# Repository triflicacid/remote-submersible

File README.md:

# Remote Control Submersible

This repository holds the custom-written software for a remote control submersible.
There is software for both the on- and off-board controllers.
Hardware overview:

- STM32 L476R chip.
- RFM98W radio module.

Both chips are configured using the STM32CubeMX IDE.

## Folder Layout

- `code` - contains various source code files.
  - `libs` contains common library files.
  - `tests` contains test projects for various components.
  - `unused` contains old unused library or miscellaneous files.
- `schematics` - contains schematics of various items, where `schematics/x` contains the KiCAD schematic sources for item `x`.
- `simulations` - contains circuit simulation files.

## Code Structure

The aim is to maximise separation between custom and generated code.
The entry point to a controller's code is in `main.c`, which provides `setup` and `loop` functions.
In the generated `main.c`, there will be a single call to `setup` with `loop` called inside an infinite loop.

There will also be files for both controllers to specify the exact configuration achieved inside STM32CubeMX.

### Shared Common

These files are copied on both controllers, although all of them are not necessarily required for a given controller.

- `action-mgr` - library for creating actions, storing as pending, and executing them.
- `communications` - types for various actions' payloads, and functions to receive payload packet.
- `counter` - library for implementing a counter with a callback.
- `dc-motor` - library for driving a DC motor.
- `lora` - library for sending and receivig data using LoRa on an RFM95/96/97/98 radio module.7
- `mcp23s17` - library for interfacing with the MCP23S17 pin extender.
- `stepper-motor` - library for driving a 4-pin stepper motor.
- `stepper-motor-event` - library for driving a stepper motor between three fixed positions.
- `stored-code` - functions to save and fetch a stored code.
- [*UNUSED*] `timed-events` - library for managing events on a timeout.
- `tm1637` - library for controlling the TM1637 segment display module.
- `util` - contains utility functions and macros.

### Common Distinct

These files are present on both controllers but contain different code (but the maintains the same semantic meaning).

- `actions` - action handlers.
- `constants` - contain implementation constants, such as pin and port configurations and names of peripherals. Creates further separation between custom and generated code.
- `globals.h` - contains global variables and types.
- `main.c` - 'entry point' of custom code; supplies `setup` and `loop` functions, and declares global variables.

### Off-Board Distinct

These files are distinct to and present only on the off-board controller.

- `7-segment` - library for arbitrary-digit full-pin 7-segment displays.
- `depth` - functions for estimating the depth of the platform.

### On-Board Distinct

These files are distinct to and present only on the on-board controller.

*None*

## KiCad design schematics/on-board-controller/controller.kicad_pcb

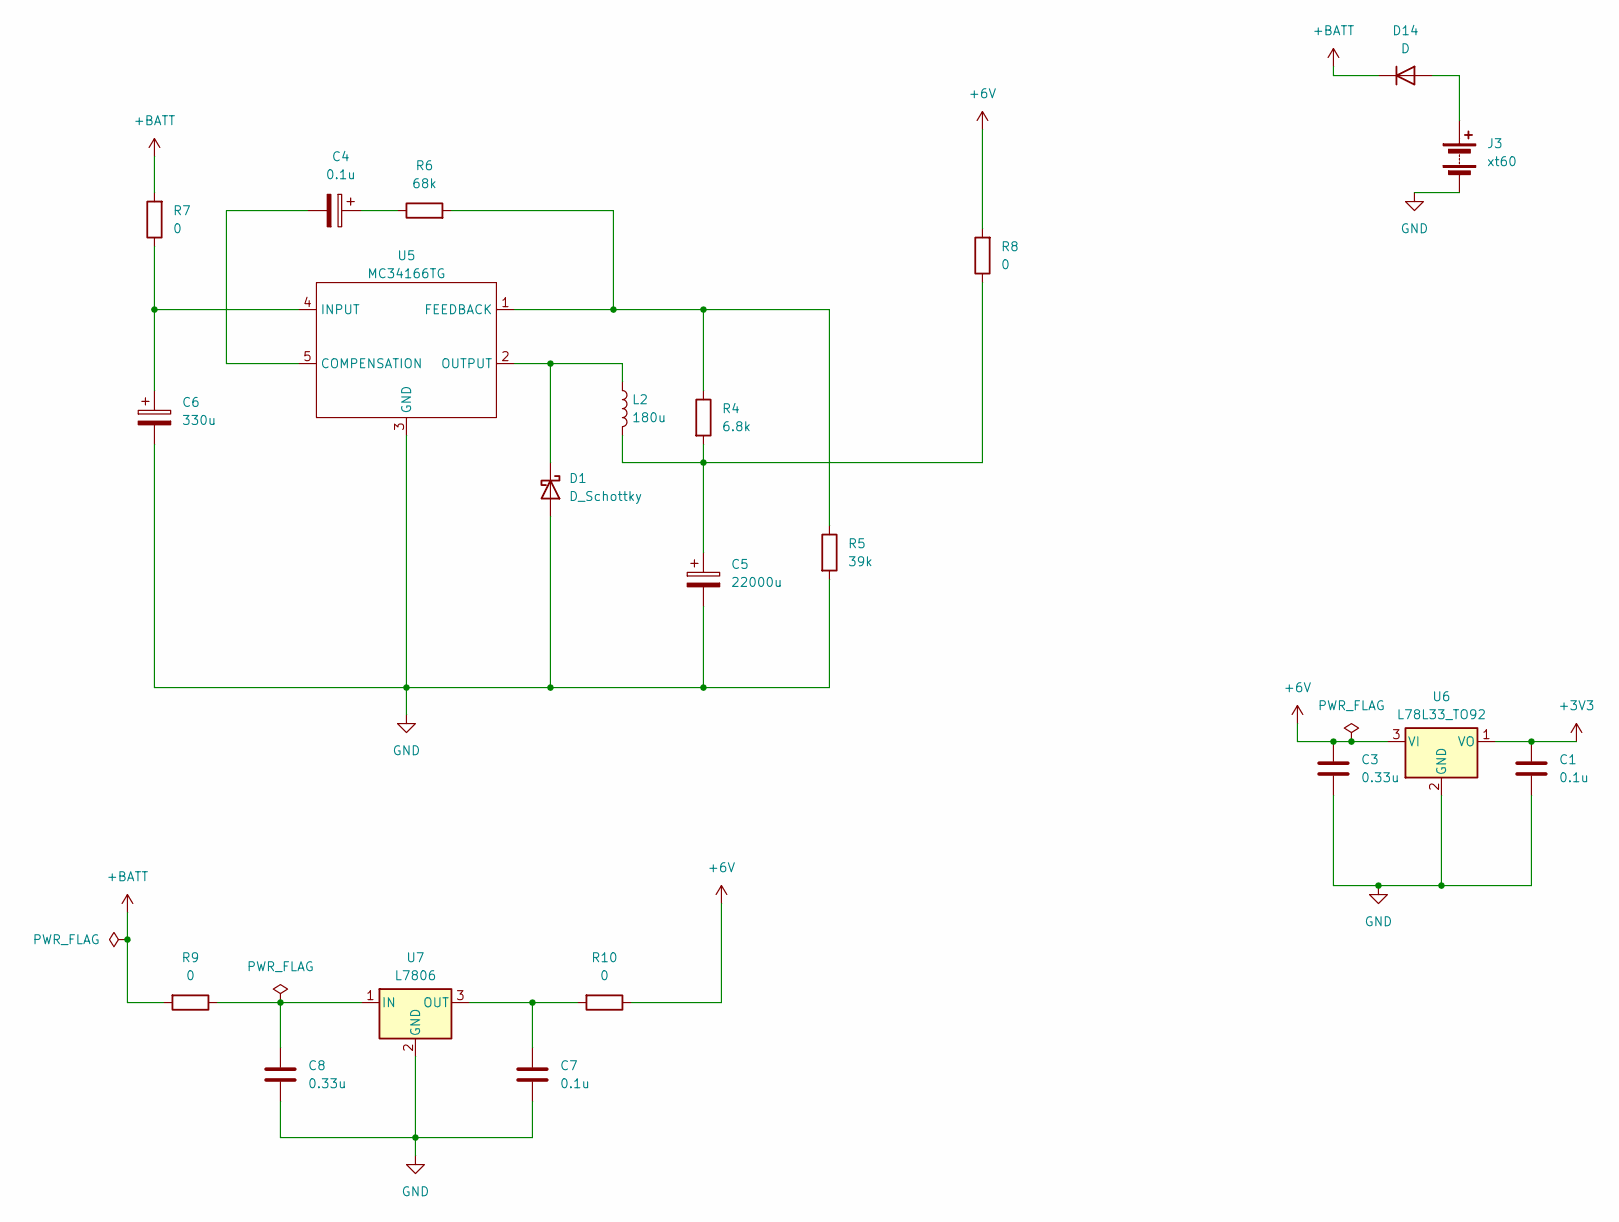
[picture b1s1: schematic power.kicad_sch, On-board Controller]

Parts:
C1, C7: 0.1u; C_0805_2012Metric_Pad1.18x1.45mm_HandSolder
C3, C8: 0.33u; C_0805_2012Metric_Pad1.18x1.45mm_HandSolder
C4: 0.1u; CP_Radial_D5.0mm_P2.00mm
C5: 22000u; CP_Radial_D18.0mm_P7.50mm
C6: 330u; CP_Radial_D8.0mm_P3.50mm
D1: D_Schottky; D_SOD-128
D14: D; D_A-405_P7.62mm_Horizontal
J3: xt60; PinSocket_1x02_P2.54mm_Vertical
L2: 180u; L_Bourns_SRR1208_12.7x12.7mm
R4: 6.8k; R_0805_2012Metric_Pad1.20x1.40mm_HandSolder
R5: 39k; R_0805_2012Metric_Pad1.20x1.40mm_HandSolder
R6: 68k; R_0805_2012Metric_Pad1.20x1.40mm_HandSolder
R7, R8, R9, R10: 0; R_0805_2012Metric_Pad1.20x1.40mm_HandSolder
U5: MC34166TG; TO-220-5_Vertical
U6: L78L33_TO92; TO-92_Inline
U7: L7806; TO-220-3_Vertical

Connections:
+3V3: C1.1, U6.1 (VO); also elsewhere on the board
+6V: C3.1, R8.2, R10.1, U6.3 (VI); also elsewhere on the board
+BATT: D14.1 (K), R7.2, R9.2; also elsewhere on the board
GND: C1.2, C3.2, C5.2, C6.2, C7.2, C8.2, D1.2 (A), J3.2 (-), R5.2, U5.3 (GND), U6.2 (GND), U7.2 (GND); also elsewhere on the board
unnamed: C4.1, R6.1
unnamed: C5.1, L2.2, R4.2, R8.1
unnamed: D1.1 (K), L2.1, U5.2 (OUTPUT)
unnamed: D14.2 (A), J3.1 (+)
unnamed: C4.2, U5.5 (COMPENSATION)
unnamed: R4.1, R5.1, R6.2, U5.1 (FEEDBACK)
unnamed: C6.1, R7.1, U5.4 (INPUT)
unnamed: C8.1, R9.1, U7.1 (IN)
unnamed: C7.1, R10.2, U7.3 (OUT)

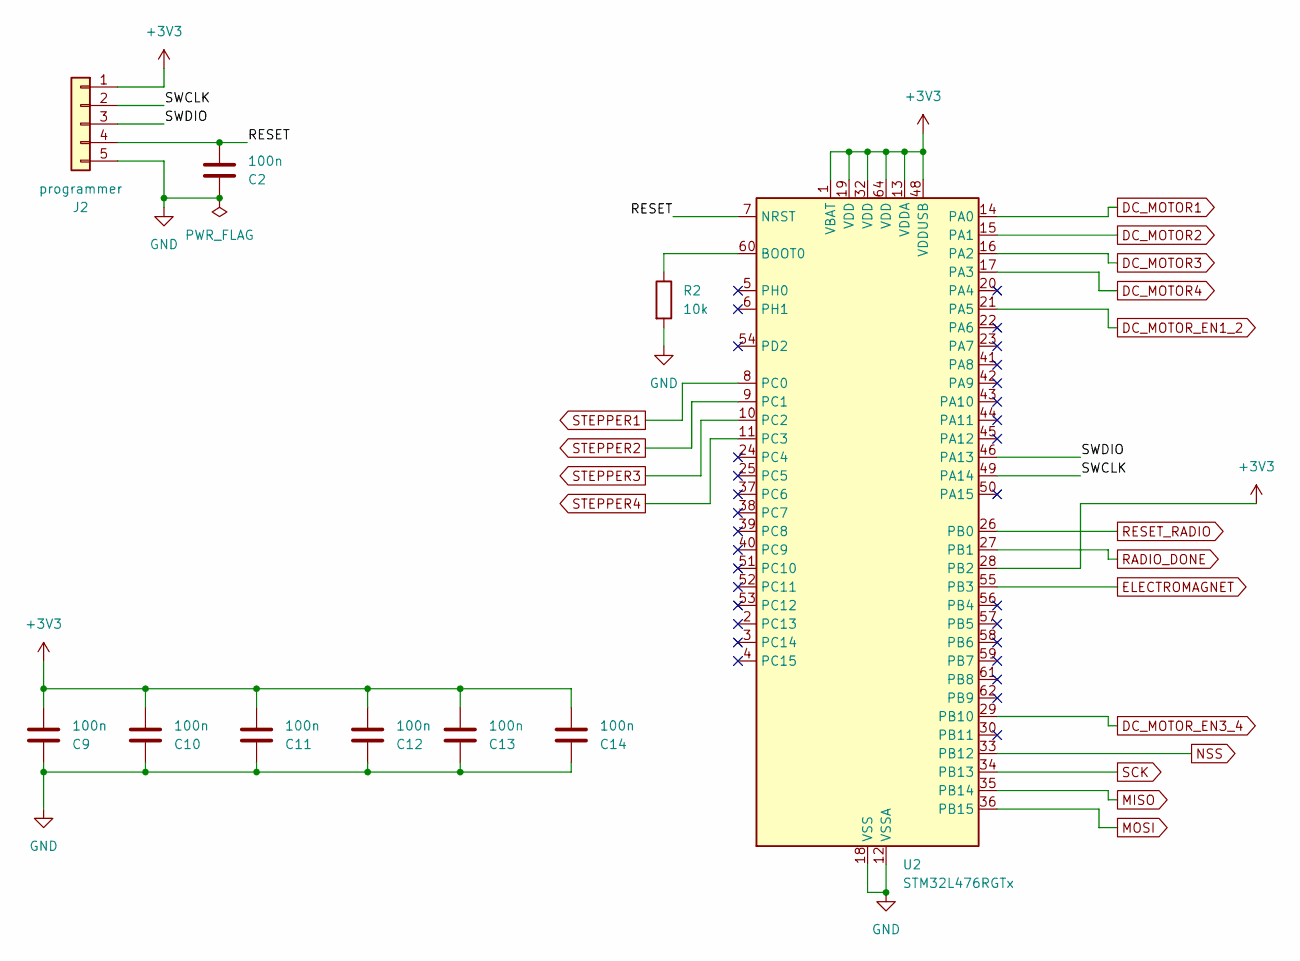
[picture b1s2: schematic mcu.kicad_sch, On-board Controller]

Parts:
C2, C9, C10, C11, C12, C13, C14: 100n; C_0805_2012Metric_Pad1.18x1.45mm_HandSolder
J2: programmer; PinSocket_1x05_P2.54mm_Vertical
R2: 10k; R_0805_2012Metric_Pad1.20x1.40mm_HandSolder
U2: STM32L476RGTx; LQFP-64_10x10mm_P0.5mm

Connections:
+3V3: C9.2, C10.2, C11.2, C12.2, C13.2, C14.2, J2.1, U2.1 (VBAT), U2.13 (VDDA), U2.19 (VDD), U2.28 (PB2), U2.32 (VDD), U2.48 (VDDUSB), U2.64 (VDD); also elsewhere on the board
/mcu/RESET: C2.2, J2.4, U2.7 (NRST)
/mcu/SWCLK: J2.2, U2.49 (PA14)
/mcu/SWDIO: J2.3, U2.46 (PA13)
DC_MOTOR1: U2.14 (PA0); also elsewhere on the board
DC_MOTOR2: U2.15 (PA1); also elsewhere on the board
DC_MOTOR3: U2.16 (PA2); also elsewhere on the board
DC_MOTOR4: U2.17 (PA3); also elsewhere on the board
DC_MOTOR_EN1_2: U2.21 (PA5); also elsewhere on the board
DC_MOTOR_EN3_4: U2.29 (PB10); also elsewhere on the board
ELECTROMAGNET: U2.55 (PB3); also elsewhere on the board
GND: C2.1, C9.1, C10.1, C11.1, C12.1, C13.1, C14.1, J2.5, R2.2, U2.12 (VSSA), U2.18 (VSS), U2.31 (VSS), U2.47 (VSS), U2.63 (VSS); also elsewhere on the board
MISO: U2.35 (PB14); also elsewhere on the board
MOSI: U2.36 (PB15); also elsewhere on the board
NSS: U2.33 (PB12); also elsewhere on the board
unnamed: R2.1, U2.60 (BOOT0)
RADIO_DONE: U2.27 (PB1); also elsewhere on the board
RESET_RADIO: U2.26 (PB0); also elsewhere on the board
SCK: U2.34 (PB13); also elsewhere on the board
STEPPER1: U2.8 (PC0); also elsewhere on the board
STEPPER2: U2.9 (PC1); also elsewhere on the board
STEPPER3: U2.10 (PC2); also elsewhere on the board
STEPPER4: U2.11 (PC3); also elsewhere on the board

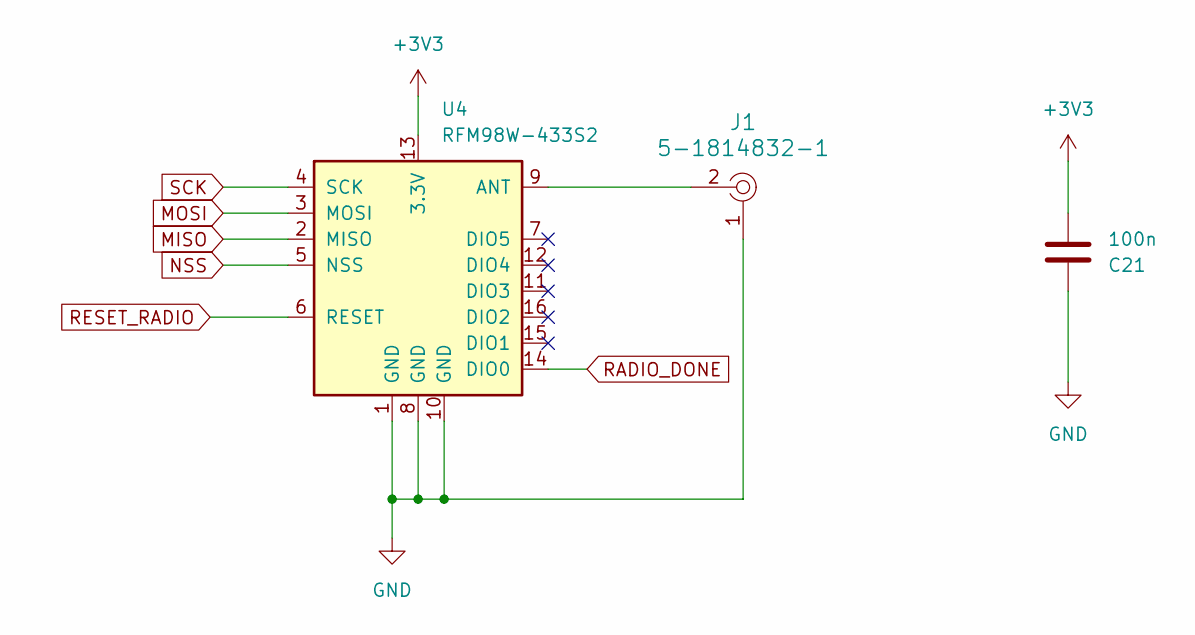
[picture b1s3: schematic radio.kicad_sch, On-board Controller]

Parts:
C21: 100n; C_0805_2012Metric_Pad1.18x1.45mm_HandSolder
J1: 5-1814832-1; RF_SMA_Vertical_5-1814832-1; MPN 5-1814832-1; Digi-Key_PN A97594-ND
U4: RFM98W-433S2; HOPERF_RFM9XW_THT

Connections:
+3V3: C21.2, U4.13 (3.3V); also elsewhere on the board
GND: C21.1, J1.1, U4.1 (GND), U4.8 (GND), U4.10 (GND); also elsewhere on the board
MISO: U4.2 (MISO); also elsewhere on the board
MOSI: U4.3 (MOSI); also elsewhere on the board
NSS: U4.5 (NSS); also elsewhere on the board
unnamed: J1.2, U4.9 (ANT)
RADIO_DONE: U4.14 (DIO0); also elsewhere on the board
RESET_RADIO: U4.6 (RESET); also elsewhere on the board
SCK: U4.4 (SCK); also elsewhere on the board

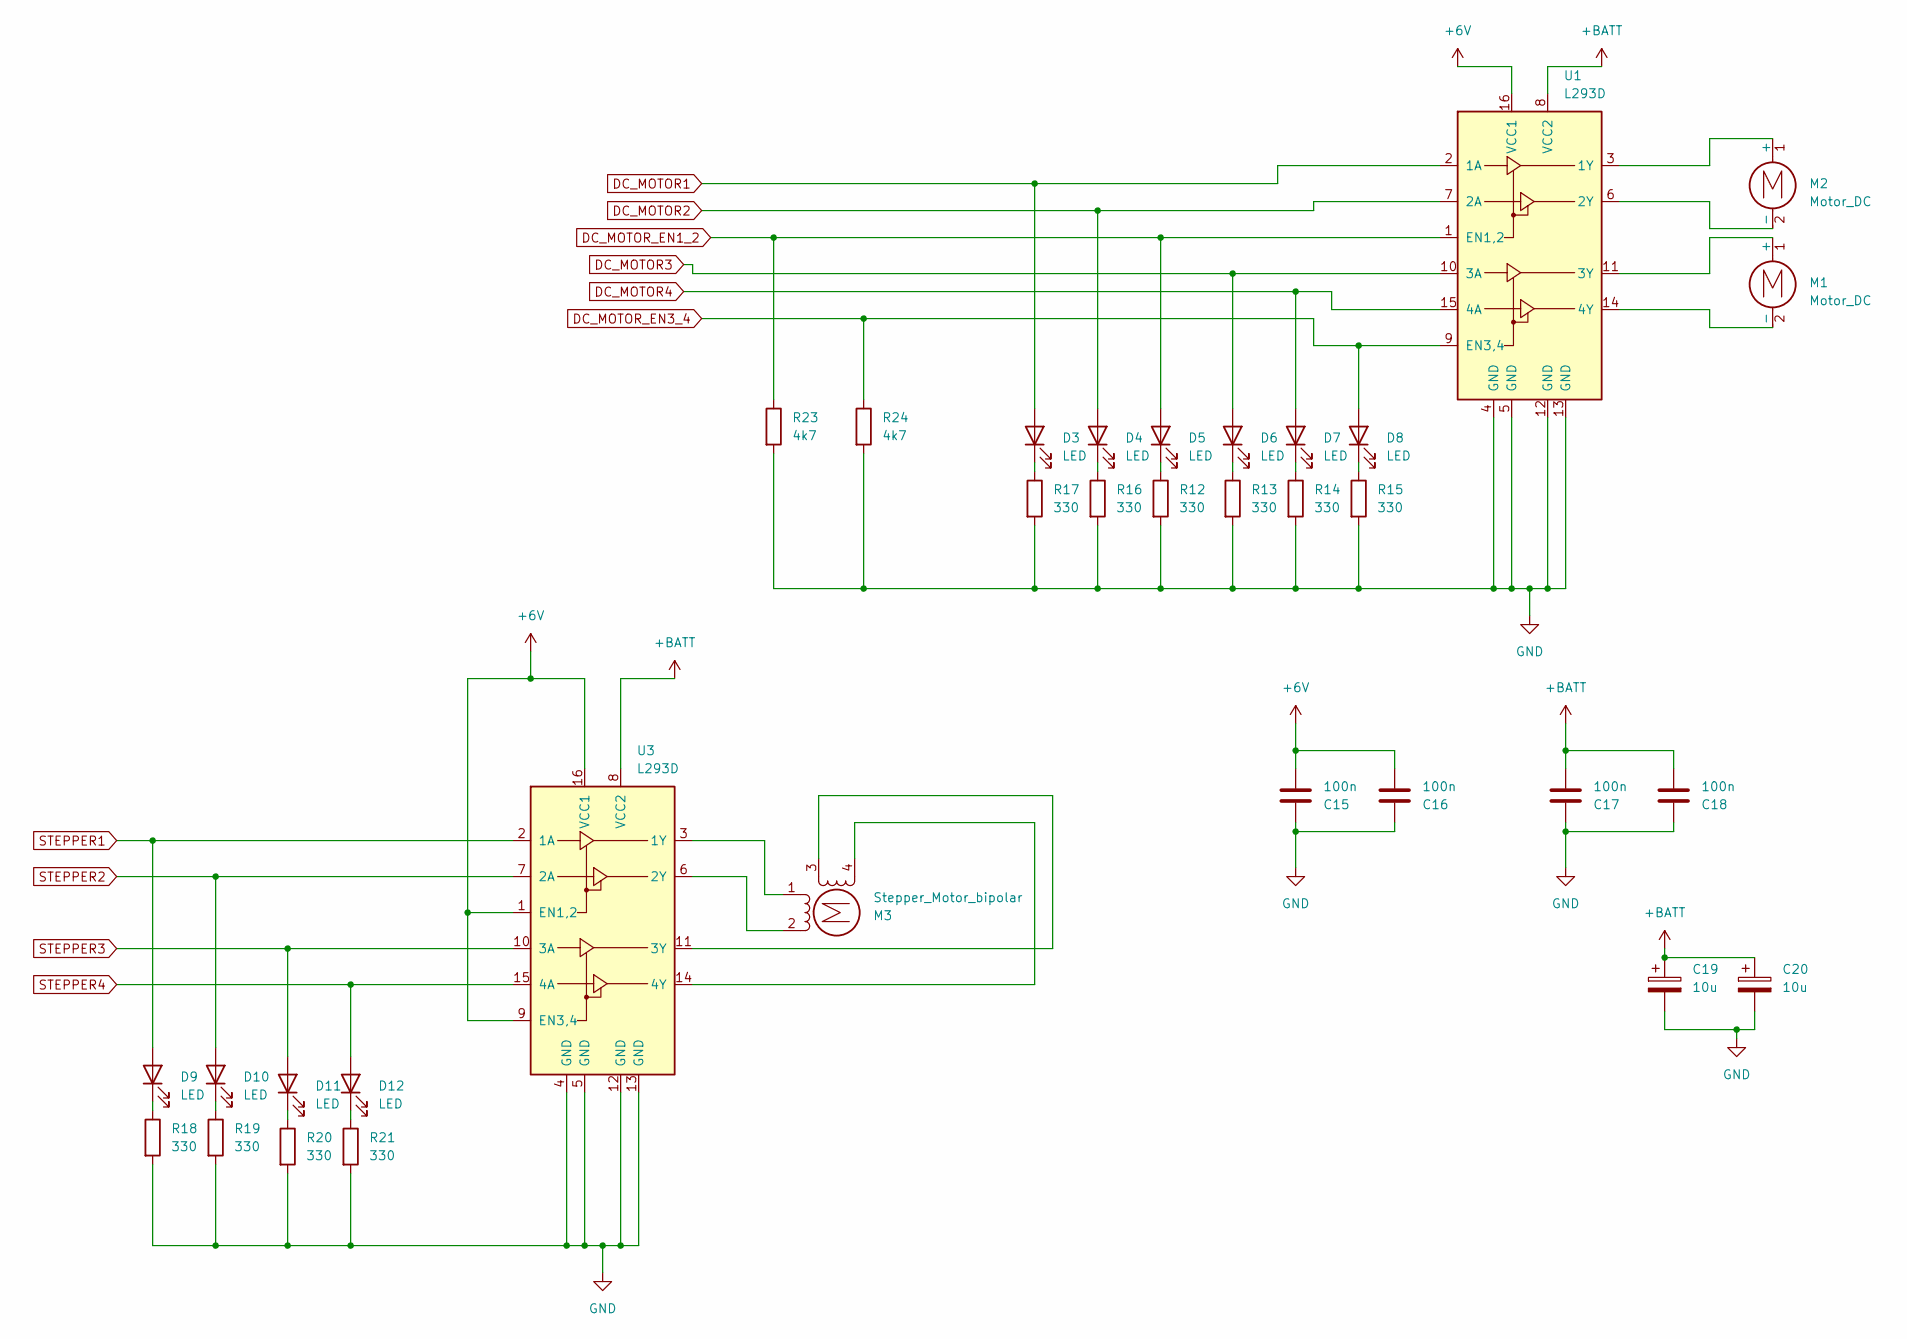
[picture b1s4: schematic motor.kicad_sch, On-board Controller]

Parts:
C15, C16, C17, C18: 100n; C_0805_2012Metric_Pad1.18x1.45mm_HandSolder
C19, C20: 10u; CP_Radial_D5.0mm_P2.50mm
D3, D4, D5, D6, D7, D8, D9, D10, D11, D12: LED; LED_0805_2012Metric_Pad1.15x1.40mm_HandSolder
M1, M2: Motor_DC; TerminalBlock_Xinya_XY308-2.54-2P_1x02_P2.54mm_Horizontal
M3: Stepper_Motor_bipolar; PinSocket_1x04_P2.54mm_Vertical
R12, R13, R14, R15, R16, R17, R18, R19, R20, R21: 330; R_0805_2012Metric_Pad1.20x1.40mm_HandSolder
R23, R24: 4k7; R_0805_2012Metric_Pad1.20x1.40mm_HandSolder
U1, U3: L293D; DIP-16_W7.62mm

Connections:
+6V: C15.2, C16.2, U1.16 (VCC1), U3.1 (EN1,2), U3.9 (EN3,4), U3.16 (VCC1); also elsewhere on the board
+BATT: C17.2, C18.2, C19.1, C20.1, U1.8 (VCC2), U3.8 (VCC2); also elsewhere on the board
DC_MOTOR1: D3.2 (A), U1.2 (1A); also elsewhere on the board
DC_MOTOR2: D4.2 (A), U1.7 (2A); also elsewhere on the board
DC_MOTOR3: D6.2 (A), U1.10 (3A); also elsewhere on the board
DC_MOTOR4: D7.2 (A), U1.15 (4A); also elsewhere on the board
DC_MOTOR_EN1_2: D5.2 (A), R23.1, U1.1 (EN1,2); also elsewhere on the board
DC_MOTOR_EN3_4: D8.2 (A), R24.1, U1.9 (EN3,4); also elsewhere on the board
GND: C15.1, C16.1, C17.1, C18.1, C19.2, C20.2, R12.2, R13.2, R14.2, R15.2, R16.2, R17.2, R18.2, R19.2, R20.2, R21.2, R23.2, R24.2, U1.4 (GND), U1.5 (GND), U1.12 (GND), U1.13 (GND), U3.4 (GND), U3.5 (GND), U3.12 (GND), U3.13 (GND); also elsewhere on the board
unnamed: D3.1 (K), R17.1
unnamed: D4.1 (K), R16.1
unnamed: D5.1 (K), R12.1
unnamed: D6.1 (K), R13.1
unnamed: D7.1 (K), R14.1
unnamed: D8.1 (K), R15.1
unnamed: D9.1 (K), R18.1
unnamed: D10.1 (K), R19.1
unnamed: D11.1 (K), R20.1
unnamed: D12.1 (K), R21.1
unnamed: M1.1 (+), U1.11 (3Y)
unnamed: M1.2 (-), U1.14 (4Y)
unnamed: M2.1 (+), U1.3 (1Y)
unnamed: M2.2 (-), U1.6 (2Y)
unnamed: M3.2 (-), U3.6 (2Y)
unnamed: M3.1, U3.3 (1Y)
unnamed: M3.3, U3.11 (3Y)
unnamed: M3.4, U3.14 (4Y)
STEPPER1: D9.2 (A), U3.2 (1A); also elsewhere on the board
STEPPER2: D10.2 (A), U3.7 (2A); also elsewhere on the board
STEPPER3: D11.2 (A), U3.10 (3A); also elsewhere on the board
STEPPER4: D12.2 (A), U3.15 (4A); also elsewhere on the board

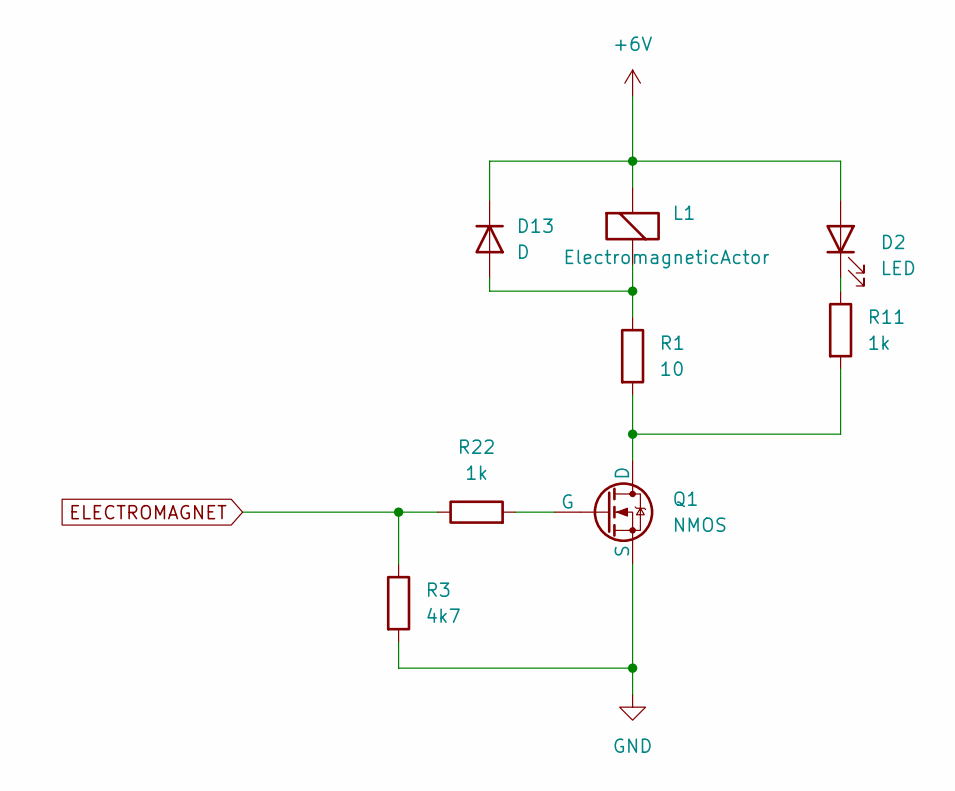
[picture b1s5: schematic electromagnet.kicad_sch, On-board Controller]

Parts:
D2: LED; LED_0805_2012Metric_Pad1.15x1.40mm_HandSolder
D13: D; LED_0805_2012Metric_Pad1.15x1.40mm_HandSolder
L1: ElectromagneticActor; TerminalBlock_Xinya_XY308-2.54-2P_1x02_P2.54mm_Horizontal
Q1: NMOS; TO-92_Inline
R1: 10; R_0805_2012Metric_Pad1.20x1.40mm_HandSolder
R3: 4k7; R_0805_2012Metric_Pad1.20x1.40mm_HandSolder
R11, R22: 1k; R_0805_2012Metric_Pad1.20x1.40mm_HandSolder

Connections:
+6V: D2.2 (A), D13.1 (K), L1.1 (-); also elsewhere on the board
ELECTROMAGNET: R3.1, R22.1; also elsewhere on the board
GND: Q1.3 (S), R3.2; also elsewhere on the board
unnamed: D2.1 (K), R11.1
unnamed: D13.2 (A), L1.2 (+), R1.1
unnamed: Q1.1 (D), R1.2, R11.2
unnamed: Q1.2 (G), R22.2

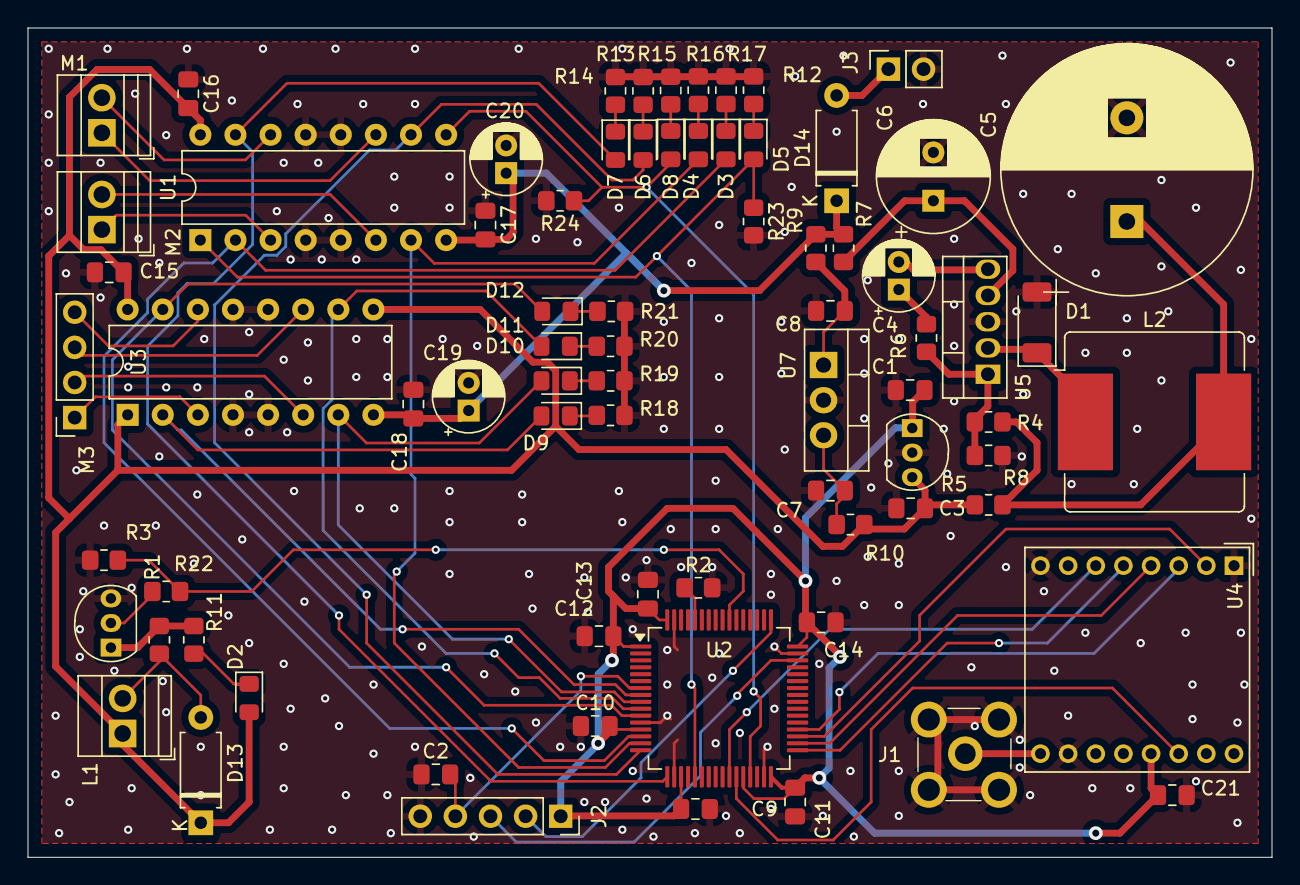
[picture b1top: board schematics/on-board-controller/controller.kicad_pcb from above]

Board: 2 copper layers, 90.0 x 60.0 mm, 75 parts (0 on the bottom side), 57 nets.

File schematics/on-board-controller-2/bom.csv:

Reference,Value,Datasheet,Footprint,Qty,supplier,code,cost per item,cost,link
,,,,,,,,,
C4,0.1u,,Capacitor_THT:CP_Radial_D5.0mm_P2.00mm,1,farnell,1902938,0.0832,0.0832,https://uk.farnell.com/multicomp-pro/mcrh100v104m5x11/cap-0-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
"C2,C9,C10,C11,C12,C13,C14,C15,C16,C17,C18,C21,C1,C7",100n,~,Capacitor_SMD:C_0805_2012Metric_Pad1.18x1.45mm_HandSolder,12,farnell,2896746,0.1812,2.1744,https://uk.farnell.com/vishay/vj0805y104kxamt/cap-0-1-f-50v-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
"C3,C8",0.33u,~,Capacitor_SMD:C_0805_2012Metric_Pad1.18x1.45mm_HandSolder,2,farnell,2520759,0.1098,0.2196,https://uk.farnell.com/kemet/c0805c334k4racauto/cap-0-33-f-1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
C5,22000u,~,Capacitor_THT:CP_Radial_D12.5mm_P5.00mm,1,farnell,1973463,4.392,4.392,https://uk.farnell.com/panasonic/eeuhd1a223/cap-22000-f-10v-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
C6,330u,~,Capacitor_THT:CP_Radial_D12.5mm_P5.00mm,1,farnell,1855174,0.6408,0.6408,https://uk.farnell.com/panasonic/eeufc1v331l/cap-330-f-35v-2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
"C19,C20",10u,~,Capacitor_THT:CP_Radial_D5.0mm_P2.00mm,2,farnell,9452036,0.093,0.186,https://uk.farnell.com/multicomp/mcrh63v106m5x11/cap-10-f-63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
D1,D_Schottky,~,Diode_THT:D_A-405_P7.62mm_Horizontal,1,farnell,2918848,0.3648,0.3648,https://uk.farnell.com/rohm/rb050lam-40tr/schottky-rect-sing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
"D2,D3,D4,D5,D6,D7,D8,D9,D10,D11,D12",LED,~,LED_SMD:LED_0805_2012Metric_Pad1.15x1.40mm_HandSolder,11,farnell,2829442,0.2796,3.0756,https://uk.farnell.com/rohm/sml-h12m8tt86c/chip-led-aec-q101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
"D13,D14",D,~,Diode_THT:D_A-405_P7.62mm_Horizontal,1,farnell,2677364,0.4068,0.4068,https://uk.farnell.com/taiwan-semiconductor/1n5398/rectifier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
J2,"programmer, xt60",~,Connector_PinSocket_2.54mm:PinSocket_1x05_P2.54mm_Vertical,1,farnell,1593461,0.2616,0.2616,https://uk.farnell.com/multicomp/2212s-05sg-85/socket-pcb-1-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
,,,,,,,,0,
"L1,M1,M2",ElectromagneticActor,~,TerminalBlock:TerminalBlock_Xinya_XY308-2.54-2P_1x02_P2.54mm_Horizontal,3,farnell,3817460,0.5832,1.7496,https://uk.farnell.com/multicomp-pro/mp008513/tb-wire-to-brd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
L2,180u,~,Inductor_SMD:L_Bourns_SRR1208_12.7x12.7mm,1,farnell,2333808,0.9252,0.9252,https://uk.farnell.com/bourns/srr1206-181kl/inductor-180uh-1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
,,,,,,,,0,
M3,Stepper_Motor_bipolar,,Connector_PinSocket_2.54mm:PinSocket_1x04_P2.54mm_Vertical,1,farnell,1593460,0.21,0.21,https://uk.farnell.com/multicomp/2212s-04sg-85/socket-pcb-1-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
,,,,,,,,0,
R1,10,~,Resistor_SMD:R_0805_2012Metric_Pad1.20x1.40mm_HandSolder,1,farnell,2073604,0.0152,0.0152,https://uk.farnell.com/multicomp/mcmr08x100-jtl/res-10r-5-0-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
R2,10k,~,Resistor_SMD:R_0805_2012Metric_Pad1.20x1.40mm_HandSolder,1,farnell,2825855,0.0886,0.0886,https://uk.farnell.com/multicomp/mchvr05ftew1002/res-10k-1-0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
"R3,R23,R24",4k7,~,Resistor_SMD:R_0805_2012Metric_Pad1.20x1.40mm_HandSolder,3,farnell,3495339,0.0203,0.0609,https://uk.farnell.com/yageo/ac0805jr-074k7l/res-4k7-5-0-125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
R4,6.8k,~,Resistor_SMD:R_0805_2012Metric_Pad1.20x1.40mm_HandSolder,1,farnell,2908421,0.0144,0.0144,https://uk.farnell.com/bourns/cr0805-fx-6801elf/res-6k8-1-08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
R5,39k,~,Resistor_SMD:R_0805_2012Metric_Pad1.20x1.40mm_HandSolder,1,farnell,2073761,0.0188,0.0188,https://uk.farnell.com/multicomp/mcmr08x3902ftl/res-39k-1-0-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
R6,68k,~,Resistor_SMD:R_0805_2012Metric_Pad1.20x1.40mm_HandSolder,1,farnell,2861918,0.0143,0.0143,https://uk.farnell.com/te-connectivity/crgcq0805j68k/res-68k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
"R7,R8,R9,R10",0,~,Resistor_SMD:R_0805_2012Metric_Pad1.20x1.40mm_HandSolder,4,farnell,9233750,0.0181,0.0724,https://uk.farnell.com/yageo/rc0805jr-070rl/res-0r0-5-0-125w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
"R11,R22",1k,~,Resistor_SMD:R_0805_2012Metric_Pad1.20x1.40mm_HandSolder,2,farnell,2861907,0.0145,0.029,https://uk.farnell.com/te-connectivity/crgcq0805j1k0/res-1k-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
"R12,R13,R14,R15,R16,R17,R18,R19,R20,R21",330,~,Resistor_SMD:R_0805_2012Metric_Pad1.20x1.40mm_HandSolder,10,farnell,2861516,0.0145,0.145,https://uk.farnell.com/te-connectivity/crgcq0805f330r/res-33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
,,,,,,,,0,
U2,STM32L476RGTx,https://www.st.com/resource/en/datasheet/stm32l476rg.pdf,Package_QFP:LQFP-64_10x10mm_P0.5mm,1,farnell,2494460,11.496,11.496,https://uk.farnell.com/stmicroelectronics/stm32l476rgt6/mcu-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
,,,,,,,,,
,,,,,,,,26.6442,

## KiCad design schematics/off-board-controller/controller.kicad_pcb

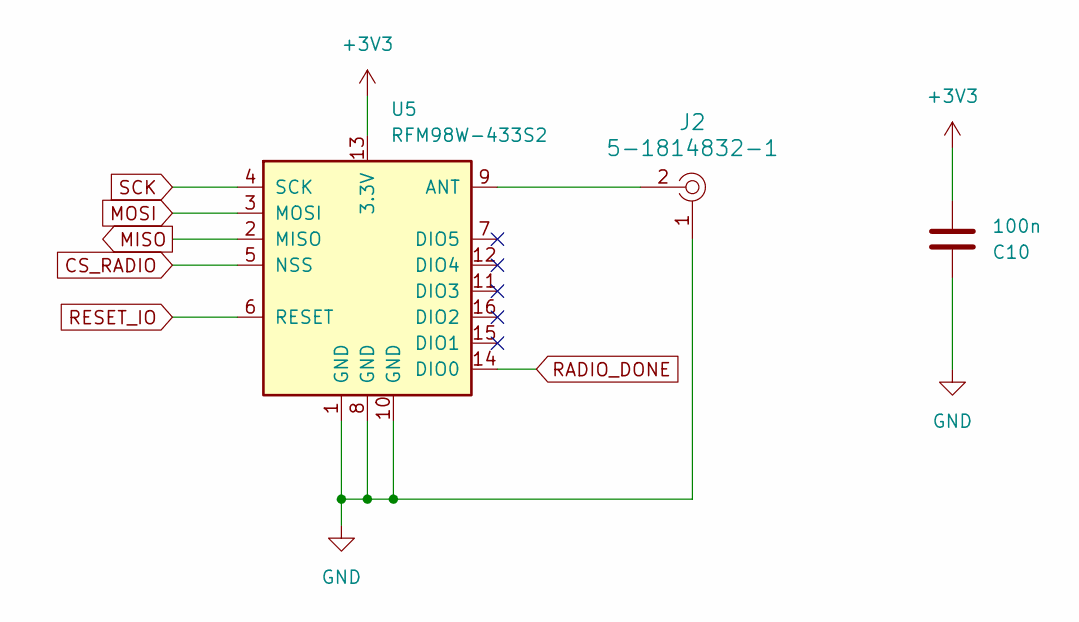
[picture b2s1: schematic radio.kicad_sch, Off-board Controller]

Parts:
C10: 100n; C_0805_2012Metric_Pad1.18x1.45mm_HandSolder
J2: 5-1814832-1; RF_SMA_Vertical_5-1814832-1; MPN 5-1814832-1; Digi-Key_PN A97594-ND
U5: RFM98W-433S2; HOPERF_RFM9XW_THT

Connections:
+3V3: C10.2, U5.13 (3.3V); also elsewhere on the board
CS_RADIO: U5.5 (NSS); also elsewhere on the board
GND: C10.1, J2.1, U5.1 (GND), U5.8 (GND), U5.10 (GND); also elsewhere on the board
MISO: U5.2 (MISO); also elsewhere on the board
MOSI: U5.3 (MOSI); also elsewhere on the board
unnamed: J2.2, U5.9 (ANT)
RADIO_DONE: U5.14 (DIO0); also elsewhere on the board
RESET_IO: U5.6 (RESET); also elsewhere on the board
SCK: U5.4 (SCK); also elsewhere on the board

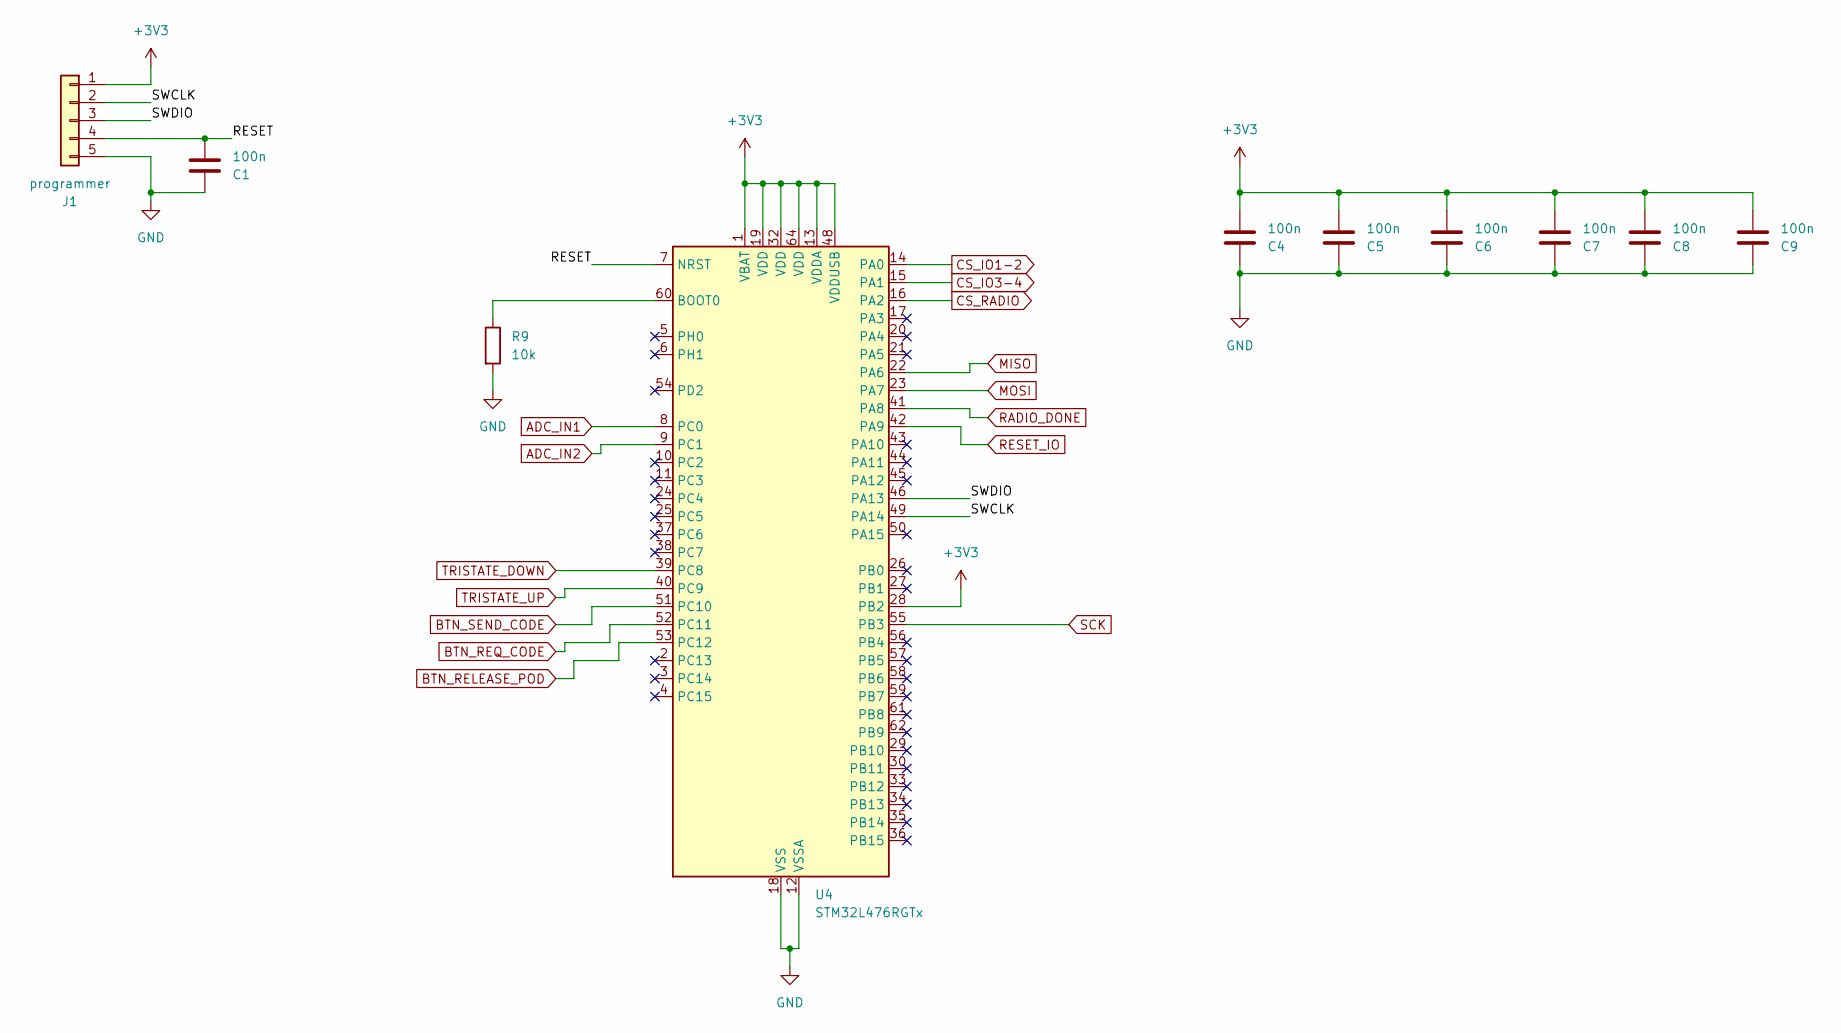
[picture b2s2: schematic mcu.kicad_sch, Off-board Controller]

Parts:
C1, C4, C5, C6, C7, C8, C9: 100n; C_0805_2012Metric_Pad1.18x1.45mm_HandSolder
J1: programmer; PinSocket_1x05_P2.54mm_Vertical
R9: 10k; R_0805_2012Metric_Pad1.20x1.40mm_HandSolder
U4: STM32L476RGTx; LQFP-64_10x10mm_P0.5mm

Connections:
+3V3: C4.2, C5.2, C6.2, C7.2, C8.2, C9.2, J1.1, U4.1 (VBAT), U4.13 (VDDA), U4.19 (VDD), U4.28 (PB2), U4.32 (VDD), U4.48 (VDDUSB), U4.64 (VDD); also elsewhere on the board
/mcu/RESET: C1.2, J1.4, U4.7 (NRST)
/mcu/SWCLK: J1.2, U4.49 (PA14)
/mcu/SWDIO: J1.3, U4.46 (PA13)
ADC_IN1: U4.8 (PC0); also elsewhere on the board
ADC_IN2: U4.9 (PC1); also elsewhere on the board
BTN_RELEASE_POD: U4.53 (PC12); also elsewhere on the board
BTN_REQ_CODE: U4.52 (PC11); also elsewhere on the board
BTN_SEND_CODE: U4.51 (PC10); also elsewhere on the board
CS_IO1-2: U4.14 (PA0); also elsewhere on the board
CS_IO3-4: U4.15 (PA1); also elsewhere on the board
CS_RADIO: U4.16 (PA2); also elsewhere on the board
GND: C1.1, C4.1, C5.1, C6.1, C7.1, C8.1, C9.1, J1.5, R9.2, U4.12 (VSSA), U4.18 (VSS), U4.31 (VSS), U4.47 (VSS), U4.63 (VSS); also elsewhere on the board
MISO: U4.22 (PA6); also elsewhere on the board
MOSI: U4.23 (PA7); also elsewhere on the board
unnamed: R9.1, U4.60 (BOOT0)
RADIO_DONE: U4.41 (PA8); also elsewhere on the board
RESET_IO: U4.42 (PA9); also elsewhere on the board
SCK: U4.55 (PB3); also elsewhere on the board
TRISTATE_DOWN: U4.39 (PC8); also elsewhere on the board
TRISTATE_UP: U4.40 (PC9); also elsewhere on the board
